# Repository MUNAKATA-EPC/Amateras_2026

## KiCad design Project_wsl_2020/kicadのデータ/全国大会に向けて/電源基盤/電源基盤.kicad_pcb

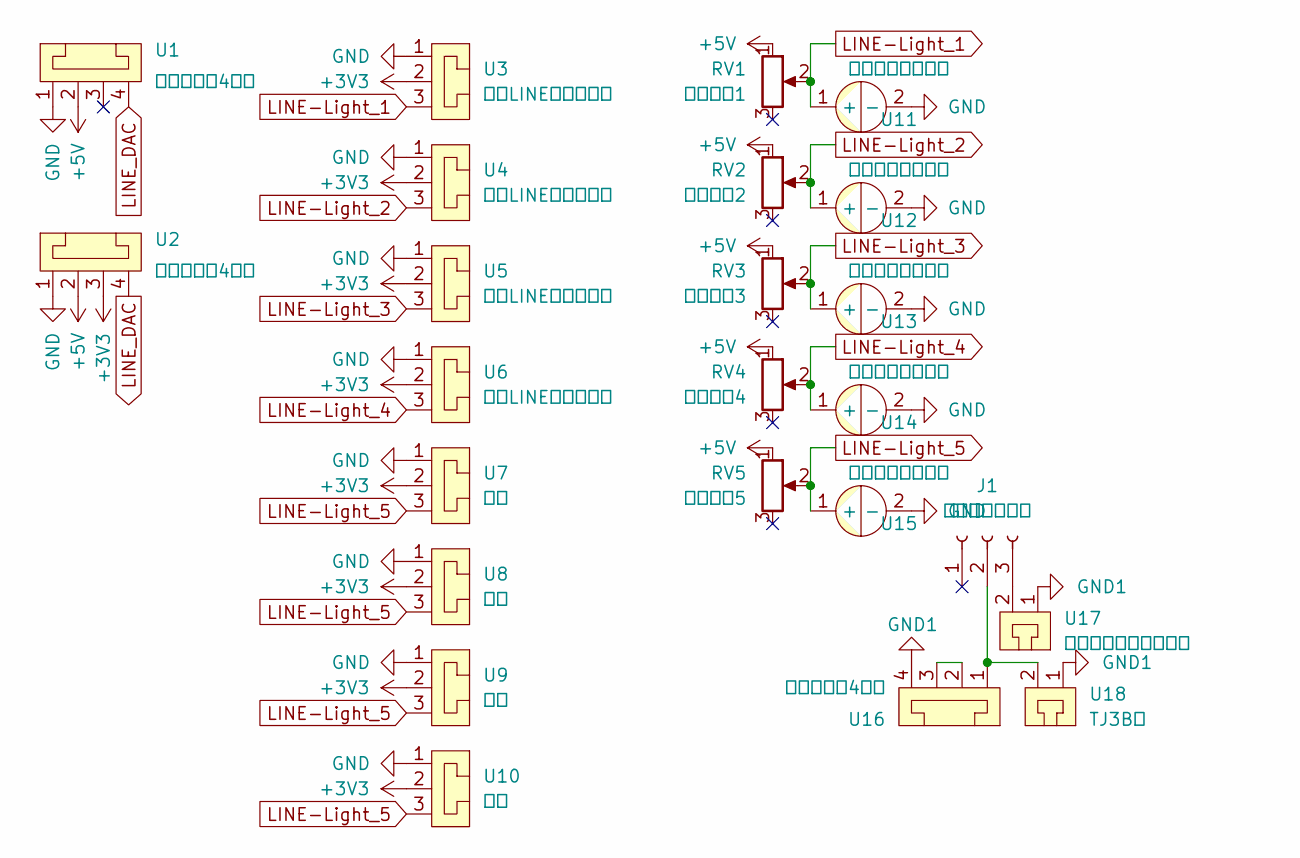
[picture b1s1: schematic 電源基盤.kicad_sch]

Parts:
J1: トグルスイッチ; 基板用大きなトグルスイッチ
RV1: 可変抵抗1; Potentiometer
RV2: 可変抵抗2; Potentiometer
RV3: 可変抵抗3; Potentiometer
RV4: 可変抵抗4; Potentiometer
RV5: 可変抵抗5; Potentiometer
U1, U2, U16: コネクター4ピン
U3: 左前LINE用コネクタ; L字コネクター3ピン
U4: 右前LINE用コネクタ; L字コネクター3ピン
U5: 左後LINE用コネクタ; L字コネクター3ピン
U6: 右後LINE用コネクタ; L字コネクター3ピン
U7, U8, U9, U10: 予備; コネクター3ピン
U11, U12, U13, U14, U15: 電解コンデンサー
U17: モータードライバー用; コネクター2ピン
U18: TJ3B用; コネクター2ピン

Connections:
+3V3: U2.3, U3.2, U4.2, U5.2, U6.2, U7.2, U8.2, U9.2, U10.2
+5V: RV1.1, RV2.1, RV3.1, RV4.1, RV5.1, U1.2, U2.2
GND: U1.1, U2.1, U3.1, U4.1, U5.1, U6.1, U7.1, U8.1, U9.1, U10.1, U11.2 (-), U12.2 (-), U13.2 (-), U14.2 (-), U15.2 (-)
GND1: U16.4, U17.1, U18.1
LINE-Light_1: RV1.2, U3.3, U11.1 (+)
LINE-Light_2: RV2.2, U4.3, U12.1 (+)
LINE-Light_3: RV3.2, U5.3, U13.1 (+)
LINE-Light_4: RV4.2, U6.3, U14.1 (+)
LINE-Light_5: RV5.2, U7.3, U8.3, U9.3, U10.3, U15.1 (+)
LINE_DAC: U1.4, U2.4
unnamed: J1.2, U16.1, U18.2
unnamed: J1.3, U17.2
unnamed: U16.2, U16.3

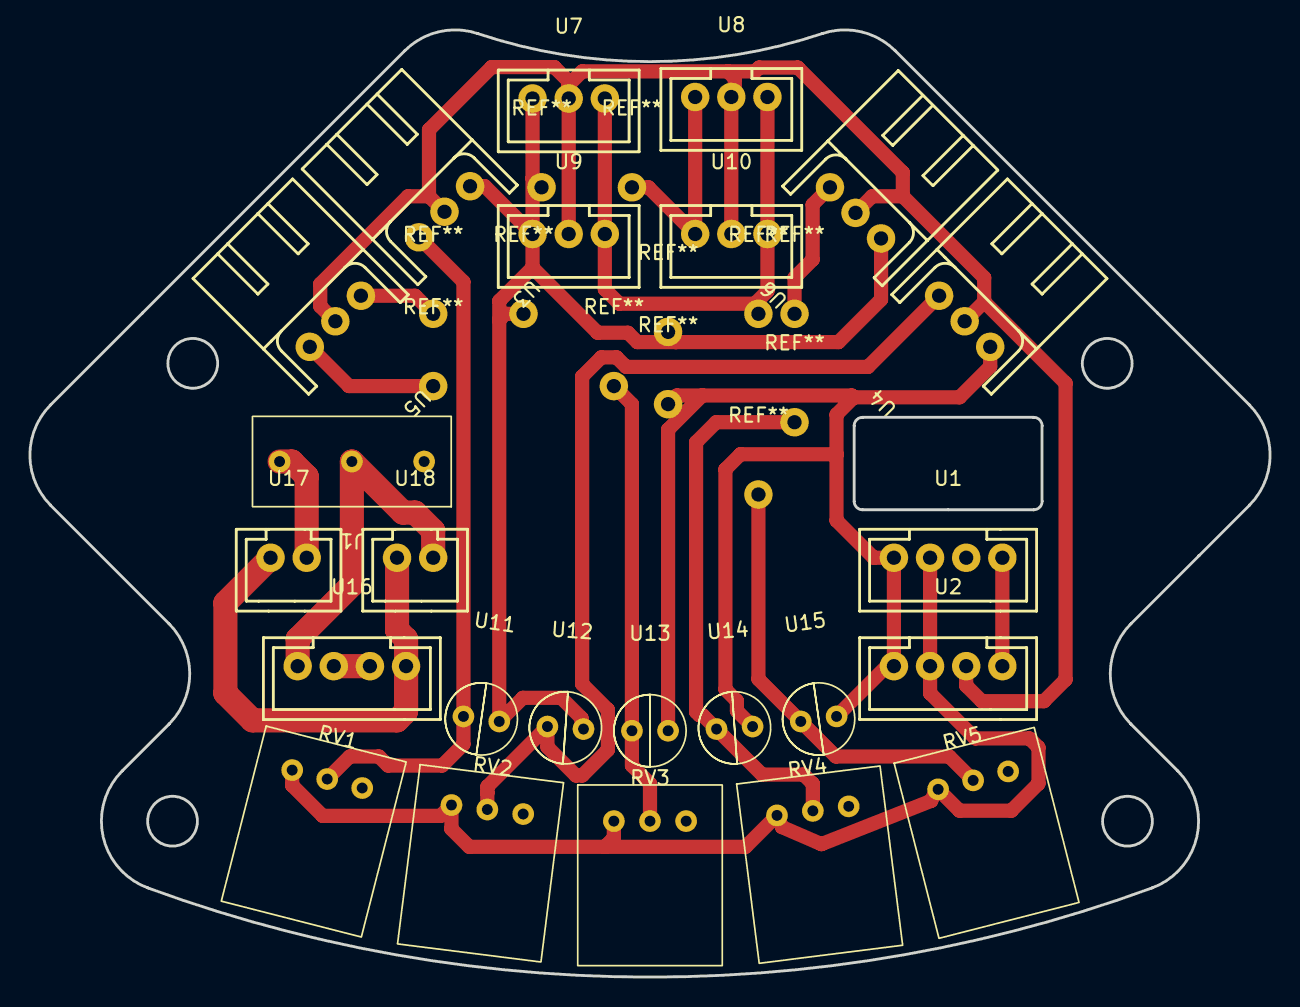
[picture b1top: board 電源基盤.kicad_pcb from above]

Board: 2 copper layers, 87.2 x 66.6 mm, 24 parts (0 on the bottom side), 13 nets.

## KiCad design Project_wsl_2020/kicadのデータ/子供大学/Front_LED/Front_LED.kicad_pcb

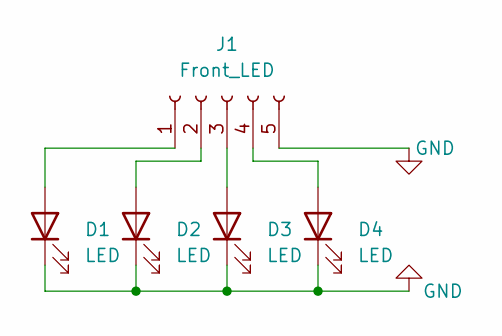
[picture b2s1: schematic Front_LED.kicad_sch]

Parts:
D1, D2, D3, D4: LED; PinSocket_1x02_P2.54mm_Horizontal
J1: Front_LED; PinSocket_1x05_P2.54mm_Vertical

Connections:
GND: D1.1 (K), D2.1 (K), D3.1 (K), D4.1 (K), J1.5
unnamed: D1.2 (A), J1.1
unnamed: D2.2 (A), J1.2
unnamed: D3.2 (A), J1.3
unnamed: D4.2 (A), J1.4

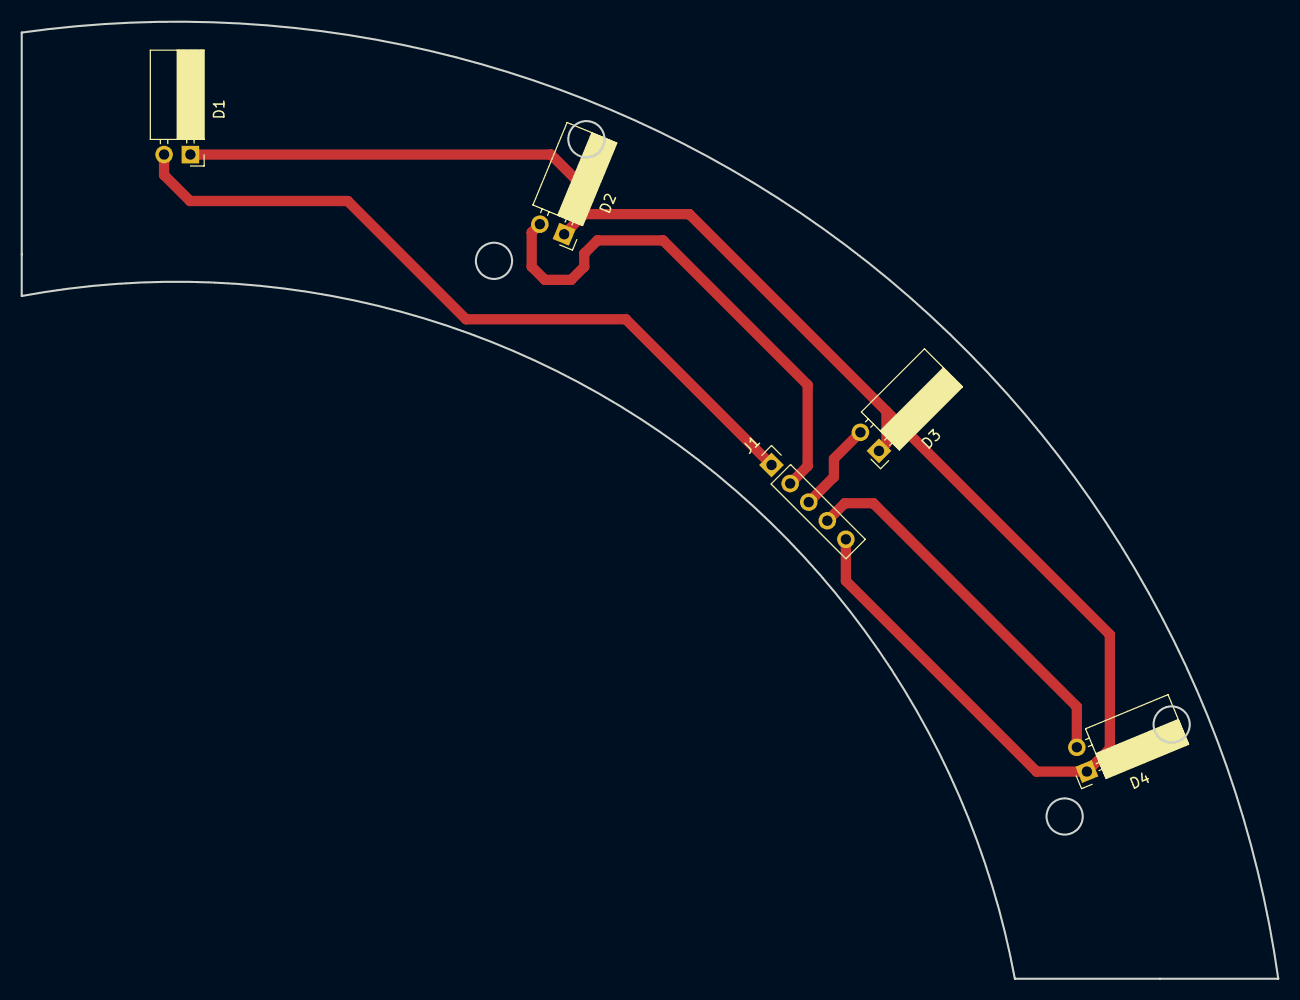
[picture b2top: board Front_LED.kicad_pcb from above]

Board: 2 copper layers, 121.4 x 92.5 mm, 5 parts (0 on the bottom side), 5 nets.
